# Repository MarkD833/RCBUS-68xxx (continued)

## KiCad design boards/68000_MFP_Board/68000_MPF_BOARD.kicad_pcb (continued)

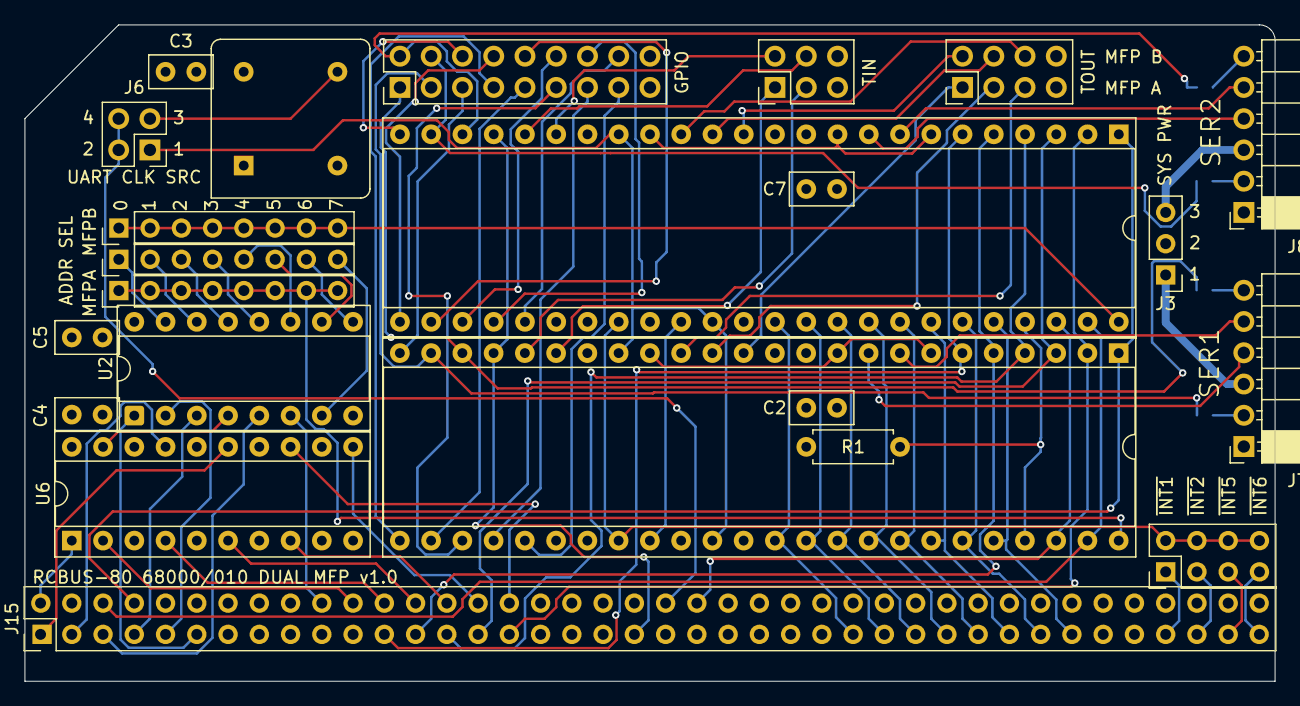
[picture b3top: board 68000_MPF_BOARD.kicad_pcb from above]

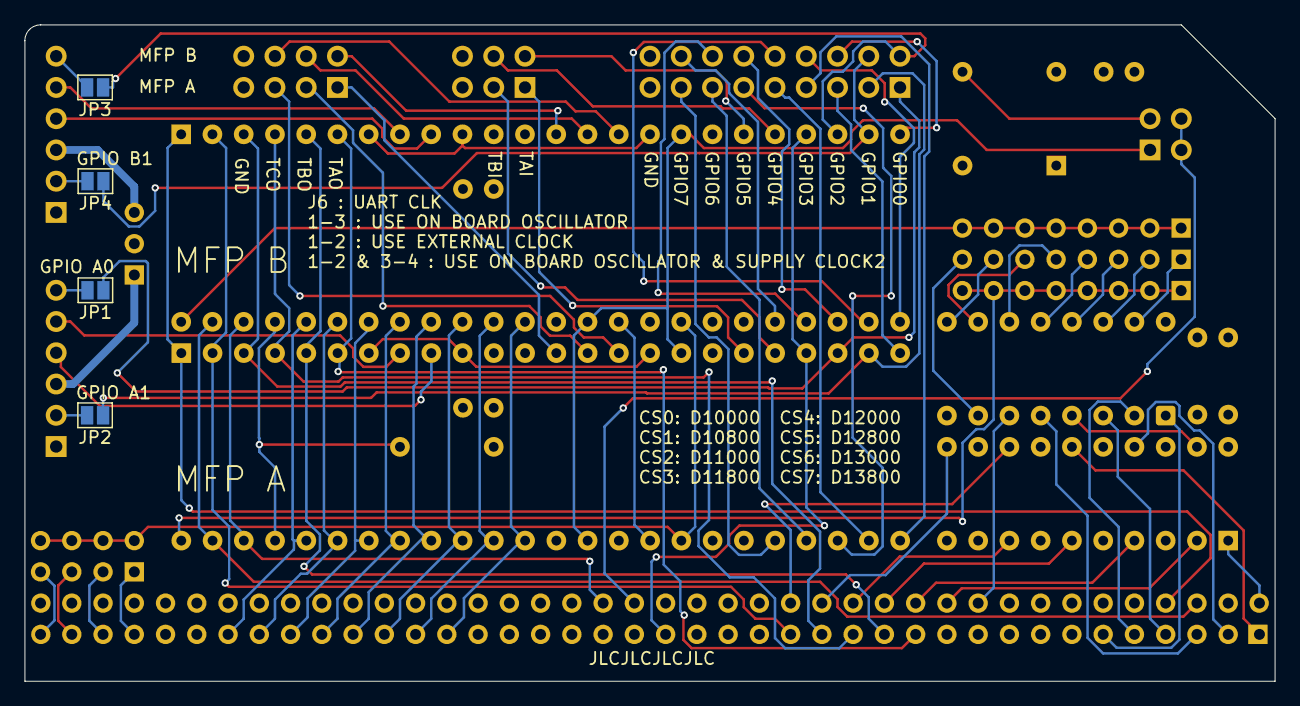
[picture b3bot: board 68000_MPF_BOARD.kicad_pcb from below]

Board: 4 copper layers, 101.6 x 53.3 mm, 27 parts (4 on the bottom side), 92 nets.

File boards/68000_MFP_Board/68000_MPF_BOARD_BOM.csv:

"Reference","Value","Datasheet","Footprint","Qty","Description"
"C2,C3,C4,C5,C7","100n","~","Capacitor_THT:C_Disc_D5.0mm_W2.5mm_P2.50mm","5","Unpolarized ceramic capacitor"
"J2,J5","Conn_02x04_Odd_Even","~","Connector_PinHeader_2.54mm:PinHeader_2x04_P2.54mm_Vertical,MyLibrary2023:PinHeader_2x04_P2.54mm_Vertical","2","Generic connector, double row, 02x04,Generic connector, double row, 02x04, right angle"
"J3","Conn_01x03","~","MyLibrary2023:PinHeader_1x03_P2.54mm_Vertical","1","Generic connector, single row, 01x03"
"J4","Conn_02x09_Odd_Even","~","Connector_PinHeader_2.54mm:PinHeader_2x09_P2.54mm_Vertical","1","Generic connector, double row, 02x09, right angle"
"J6","Conn_02x02_Odd_Even","~","Connector_PinHeader_2.54mm:PinHeader_2x02_P2.54mm_Vertical","1","Generic connector, double row, 02x02"
"J7,J8","Conn_01x06","~","Connector_PinSocket_2.54mm:PinSocket_1x06_P2.54mm_Horizontal","2","Generic connector, single row, 01x06, right angle"
"J9,J11,J12","Conn_01x08","~","MyLibrary2023:PinHeader_1x08_P2.54mm_Vertical","3","Generic connector, single row, 01x08"
"J14","Conn_02x03_Odd_Even","~","Connector_PinHeader_2.54mm:PinHeader_2x03_P2.54mm_Vertical","1","Generic connector, double row, 02x03, right angle"
"J15","RCBus_80PIN_68000","~","MyLibrary2023:RCBus_80p_Medium","1","Generic connector, double row, 02x20, right angle"
"JP1,JP2,JP3,JP4","SolderJumper","~","Jumper:SolderJumper-2_P1.3mm_Open_Pad1.0x1.5mm","4","Solder Jumper, 2-pole, open"
"R1","10K","~","Resistor_THT:R_Axial_DIN0207_L6.3mm_D2.5mm_P7.62mm_Horizontal","1",""
"U2","74LS138","http://www.ti.com/lit/gpn/sn74LS138","Package_DIP:DIP-16_W7.62mm_Socket","1","Decoder 3 to 8 active low outputs"
"U4,U5","68901P","","MyLibrary2023:DIP-48_W15.24mm_Socket","2","Multi-function peripheral device"
"U6","74LS688","http://www.ti.com/lit/gpn/sn74LS688","MyLibrary2023:DIP-20_W7.62mm_Socket","1","8-bit magnitude comparator"
"X1","CXO_DIP8","http://cdn-reichelt.de/documents/datenblatt/B400/OSZI.pdf","Oscillator:Oscillator_DIP-8","1","Crystal Clock Oscillator, DIP8-style metal package"

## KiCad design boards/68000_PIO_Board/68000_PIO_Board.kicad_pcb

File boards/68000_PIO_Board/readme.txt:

For some reason that I can't yet figure out, the 68230 board is very unreliable. The issue seems to be with the write timing as the chips always report the correct port pin levels during a read of the alternate data registers.

I've tried 68230s from ST and Mostek with a simple test program with the timer configured to output a square wave on PC3 whilst also toggling pin PA0 in software. I'm getting all combinations of results from no pin activity, only PA0 toggles, only PC3 toggles and both PA0 and PC3 toggling.

I know the code works as a PLCC 68230 (Freescale badged) on another 68000 system I have works correctly.

NOTE:
=====
* The 68230 needs a clock signal in order to function correctly, even if the
  timer is not being used. Set J2 and J6 for your choice of clock source.

ERRORS:
======= 
* The 68230 chip select has to include one of the /nDS signals not just /AS.
  Fix by cutting the /AS track between RCBus pin 41 and the 74LS688 pin 1.
  Add a wire link between RCBus pin 43 (/LDS) and the 74LS688 pin 1.

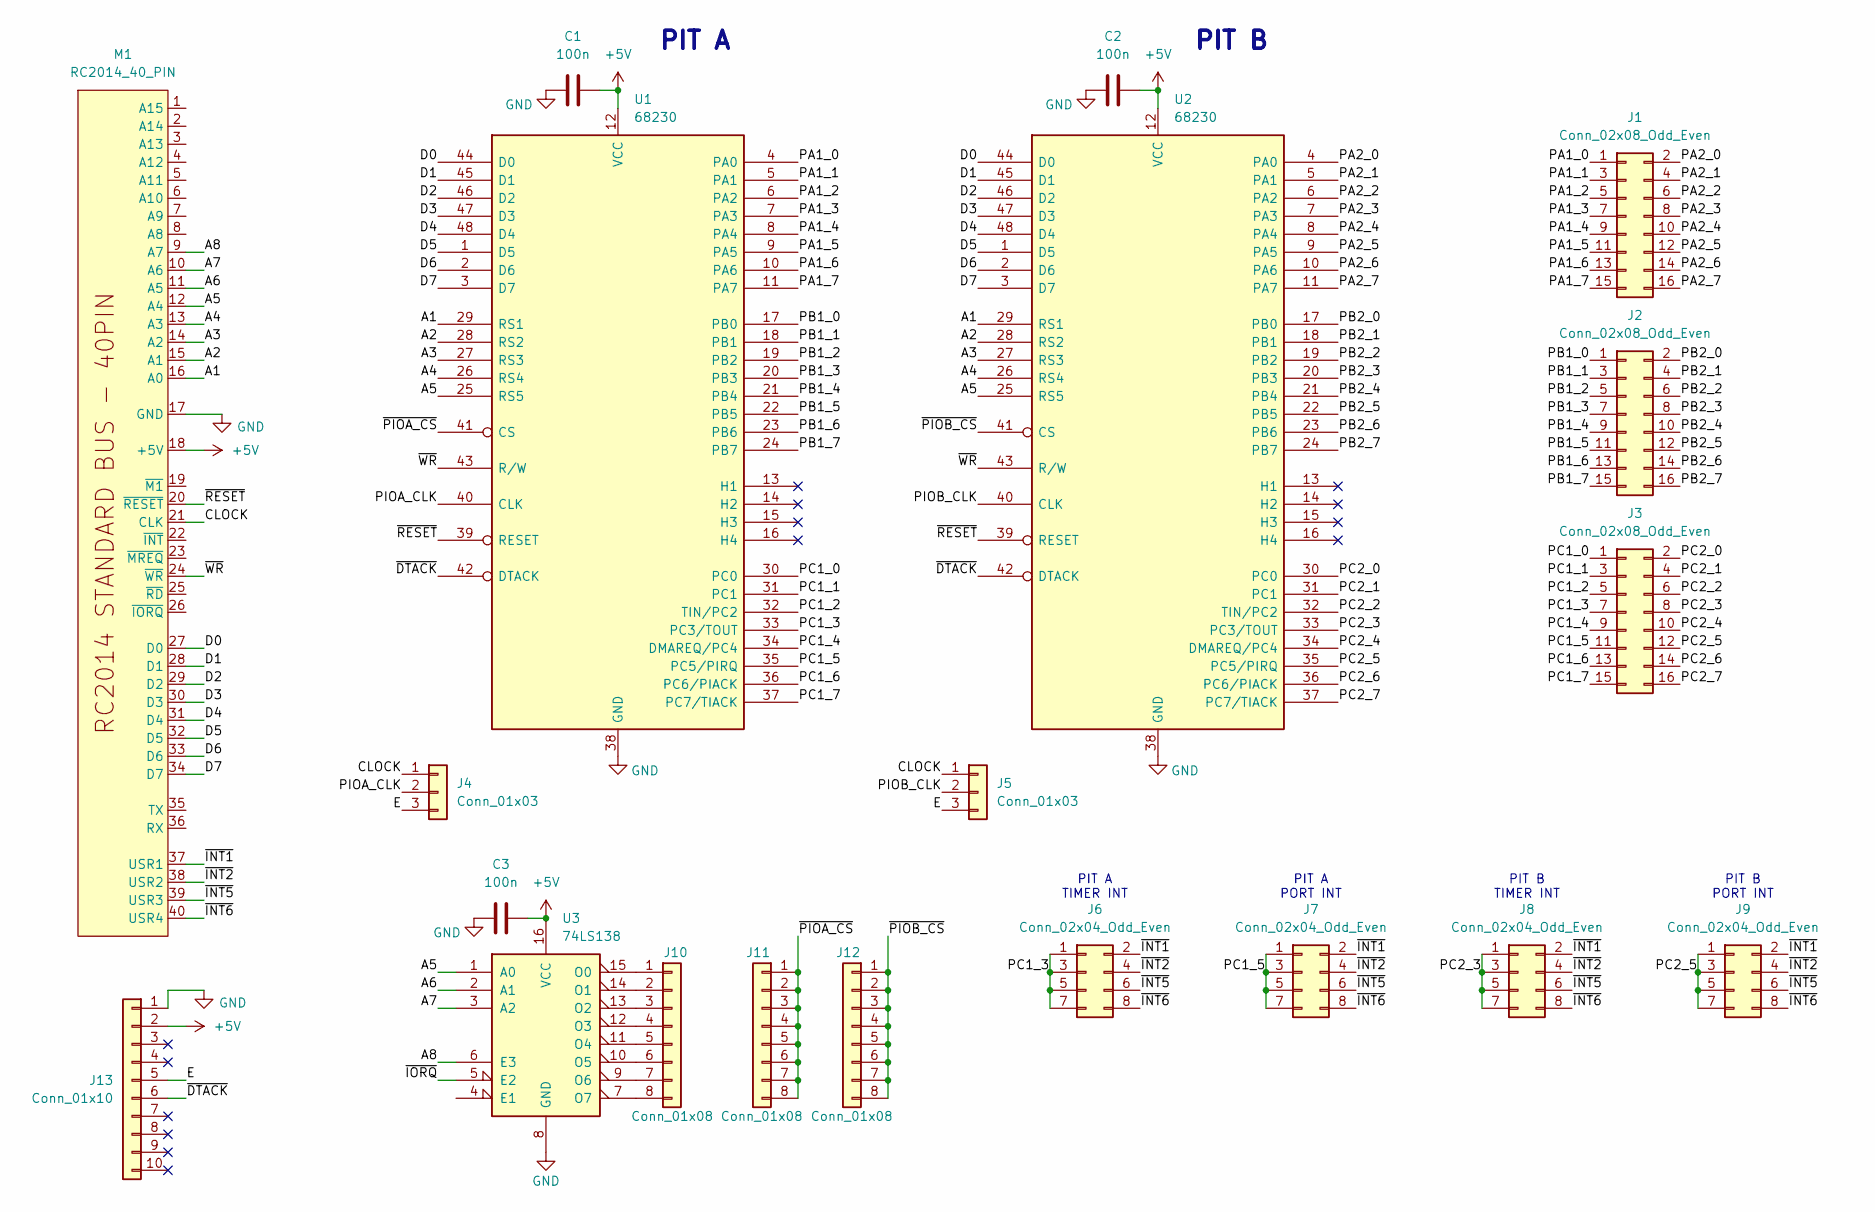
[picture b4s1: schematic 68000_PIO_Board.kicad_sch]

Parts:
C1, C2, C3: 100n; C_Disc_D5.0mm_W2.5mm_P2.50mm
J1, J2, J3: Conn_02x08_Odd_Even; PinHeader_2x08_P2.54mm_Vertical
J4, J5: Conn_01x03; PinHeader_1x03_P2.54mm_Vertical
J6, J7, J8, J9: Conn_02x04_Odd_Even; PinHeader_2x04_P2.54mm_Vertical
J10, J11, J12: Conn_01x08; PinHeader_1x08_P2.54mm_Vertical
J13: Conn_01x10; PinHeader_1x10_P2.54mm_Vertical
M1: RC2014_40_PIN; RC2014_STD_40_PIN
U1, U2: 68230; DIP-48_W15.24mm_Socket
U3: 74LS138; DIP-16_W7.62mm_Socket

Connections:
+5V: C1.1, C2.1, C3.2, J13.2, M1.18 (+5V), U1.12 (VCC), U2.12 (VCC), U3.16 (VCC)
/A1: M1.16 (A0), U1.29 (RS1), U2.29 (RS1)
/A2: M1.15 (A1), U1.28 (RS2), U2.28 (RS2)
/A3: M1.14 (A2), U1.27 (RS3), U2.27 (RS3)
/A4: M1.13 (A3), U1.26 (RS4), U2.26 (RS4)
/A5: M1.12 (A4), U1.25 (RS5), U2.25 (RS5), U3.1 (A0)
/A6: M1.11 (A5), U3.2 (A1)
/A7: M1.10 (A6), U3.3 (A2)
/A8: M1.9 (A7), U3.6 (E3)
/CLOCK: J4.1, J5.1, M1.21 (CLK)
/D0: M1.27 (D0), U1.44 (D0), U2.44 (D0)
/D1: M1.28 (D1), U1.45 (D1), U2.45 (D1)
/D2: M1.29 (D2), U1.46 (D2), U2.46 (D2)
/D3: M1.30 (D3), U1.47 (D3), U2.47 (D3)
/D4: M1.31 (D4), U1.48 (D4), U2.48 (D4)
/D5: M1.32 (D5), U1.1 (D5), U2.1 (D5)
/D6: M1.33 (D6), U1.2 (D6), U2.2 (D6)
/D7: M1.34 (D7), U1.3 (D7), U2.3 (D7)
/E: J4.3, J5.3, J13.5
/PA1_0: J1.1, U1.4 (PA0)
/PA1_1: J1.3, U1.5 (PA1)
/PA1_2: J1.5, U1.6 (PA2)
/PA1_3: J1.7, U1.7 (PA3)
/PA1_4: J1.9, U1.8 (PA4)
/PA1_5: J1.11, U1.9 (PA5)
/PA1_6: J1.13, U1.10 (PA6)
/PA1_7: J1.15, U1.11 (PA7)
/PA2_0: J1.2, U2.4 (PA0)
/PA2_1: J1.4, U2.5 (PA1)
/PA2_2: J1.6, U2.6 (PA2)
/PA2_3: J1.8, U2.7 (PA3)
/PA2_4: J1.10, U2.8 (PA4)
/PA2_5: J1.12, U2.9 (PA5)
/PA2_6: J1.14, U2.10 (PA6)
/PA2_7: J1.16, U2.11 (PA7)
/PB1_0: J2.1, U1.17 (PB0)
/PB1_1: J2.3, U1.18 (PB1)
/PB1_2: J2.5, U1.19 (PB2)
/PB1_3: J2.7, U1.20 (PB3)
/PB1_4: J2.9, U1.21 (PB4)
/PB1_5: J2.11, U1.22 (PB5)
/PB1_6: J2.13, U1.23 (PB6)
/PB1_7: J2.15, U1.24 (PB7)
/PB2_0: J2.2, U2.17 (PB0)
/PB2_1: J2.4, U2.18 (PB1)
/PB2_2: J2.6, U2.19 (PB2)
/PB2_3: J2.8, U2.20 (PB3)
/PB2_4: J2.10, U2.21 (PB4)
/PB2_5: J2.12, U2.22 (PB5)
/PB2_6: J2.14, U2.23 (PB6)
/PB2_7: J2.16, U2.24 (PB7)
/PC1_0: J3.1, U1.30 (PC0)
/PC1_1: J3.3, U1.31 (PC1)
/PC1_2: J3.5, U1.32 (TIN/PC2)
/PC1_3: J3.7, J6.1, J6.3, J6.5, J6.7, U1.33 (PC3/TOUT)
/PC1_4: J3.9, U1.34 (DMAREQ/PC4)
/PC1_5: J3.11, J7.1, J7.3, J7.5, J7.7, U1.35 (PC5/PIRQ)
/PC1_6: J3.13, U1.36 (PC6/PIACK)
/PC1_7: J3.15, U1.37 (PC7/TIACK)
/PC2_0: J3.2, U2.30 (PC0)
/PC2_1: J3.4, U2.31 (PC1)
/PC2_2: J3.6, U2.32 (TIN/PC2)
/PC2_3: J3.8, J8.1, J8.3, J8.5, J8.7, U2.33 (PC3/TOUT)
/PC2_4: J3.10, U2.34 (DMAREQ/PC4)
/PC2_5: J3.12, J9.1, J9.3, J9.5, J9.7, U2.35 (PC5/PIRQ)
/PC2_6: J3.14, U2.36 (PC6/PIACK)
/PC2_7: J3.16, U2.37 (PC7/TIACK)
/PIOA_CLK: J4.2, U1.40 (CLK)
/PIOB_CLK: J5.2, U2.40 (CLK)
/~DTACK: J13.6, U1.42 (DTACK), U2.42 (DTACK)
/~INT1: J6.2, J7.2, J8.2, J9.2, M1.37 (USR1)
/~INT2: J6.4, J7.4, J8.4, J9.4, M1.38 (USR2)
/~INT5: J6.6, J7.6, J8.6, J9.6, M1.39 (USR3)
/~INT6: J6.8, J7.8, J8.8, J9.8, M1.40 (USR4)
/~IORQ: U3.5 (E2)
/~PIOA_CS: J11.1, J11.2, J11.3, J11.4, J11.5, J11.6, J11.7, J11.8, U1.41 (CS)
/~PIOB_CS: J12.1, J12.2, J12.3, J12.4, J12.5, J12.6, J12.7, J12.8, U2.41 (CS)
/~RESET: M1.20 (~RESET), U1.39 (RESET), U2.39 (RESET)
/~WR: M1.24 (~WR), U1.43 (R/W), U2.43 (R/W)
GND: C1.2, C2.2, C3.1, J13.1, M1.17 (GND), U1.38 (GND), U2.38 (GND), U3.8 (GND)
unnamed: J10.1, U3.15 (O0)
unnamed: J10.2, U3.14 (O1)
unnamed: J10.3, U3.13 (O2)
unnamed: J10.4, U3.12 (O3)
unnamed: J10.5, U3.11 (O4)
unnamed: J10.6, U3.10 (O5)
unnamed: J10.7, U3.9 (O6)
unnamed: J10.8, U3.7 (O7)

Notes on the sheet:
PIT B PORT INT
PIT A PORT INT
PIT B
PIT A TIMER INT
PIT B TIMER INT
PIT A

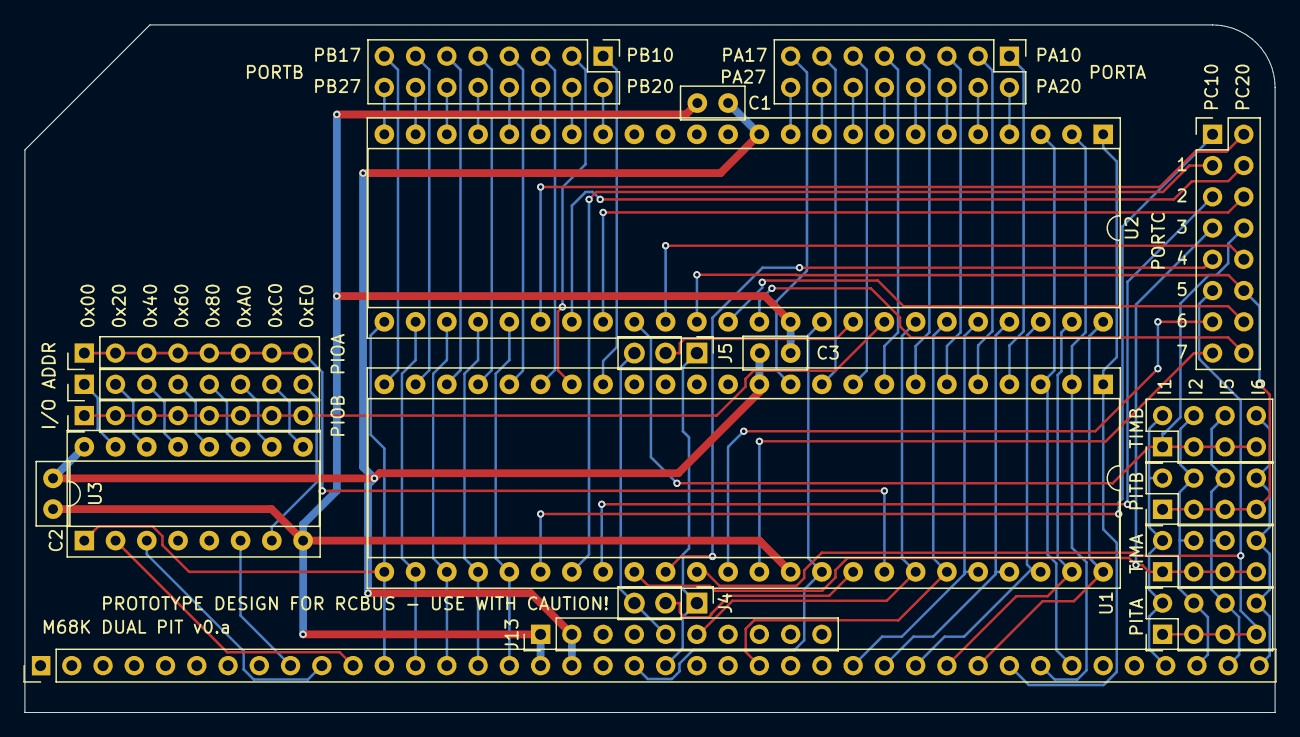
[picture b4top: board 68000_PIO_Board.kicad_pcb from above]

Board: 2 copper layers, 101.6 x 55.9 mm, 20 parts (0 on the bottom side), 87 nets.

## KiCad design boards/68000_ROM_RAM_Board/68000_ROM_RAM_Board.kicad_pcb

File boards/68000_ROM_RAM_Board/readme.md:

# ROM & RAM board - V1 - 128K ROM + 1M RAM

# Details
The ROM & RAM board is designed to plug into an RCBus-80 backplane with support for 128K ROM (via 2x Winbond W27C512 EEPROMs) and 1M RAM (via 2x Alliance Memory AS6C4008 SRAMs). The EEPROMs and SRAMs are used as a pair to allow 16-bit wide memory accesses.

## Address Decoding
The address decoding is carried out by a 74LS138 and divides the lower 8Mb of memory space into eight 1Mb blocks. The EEPROMs are hard wired to /CS0 (pin 15) and the SRAMs are hard wired to /CS1 (pin 14). This configuration always places the EEPROMs starting at address 0x000000 and the SRAMs starting at address 0x100000.

## Bus Width 
A 74LS139 generates the read and write signals for each of the memory chips and takes care of byte or word accesses.

## DTACK
A 74LS125 is used to generate a simple /DTACK signal driven directly from the EEPROM and SRAM chip select signals without any wait period.

# Board Assembly
Assembly of the board should be fairly straightforward as there are no surface mount devices to deal with.

When fitting the 80-pin right angle connector, initially only solder a couple of pins at opposite ends of the connector so that you can make any adjustments if the board is not vertical when fitted to the backplane.

# Winbond W27C512 EEPROMs
Be careful where you source these devices from. I bought mine from AliExpress and they were sold as new. In fact they were salvaged from boards and the IC legs were tinned with solder. This makes the pins slightly "sticky" when you insert the chips into IC sockets. My experience with these chips is that you may get 6-10 insertions/removals before the IC socket spring contacts start to break.

# Errors
None so far.

# To Do
+ Experiment to find the maximum width of board that JLCPCB will accept to keep the low price.
+ Modify the RCBus80 medium board footprint in Kicad so that pins 1,40,41 & 80 don't throw DRC warnings/errors.

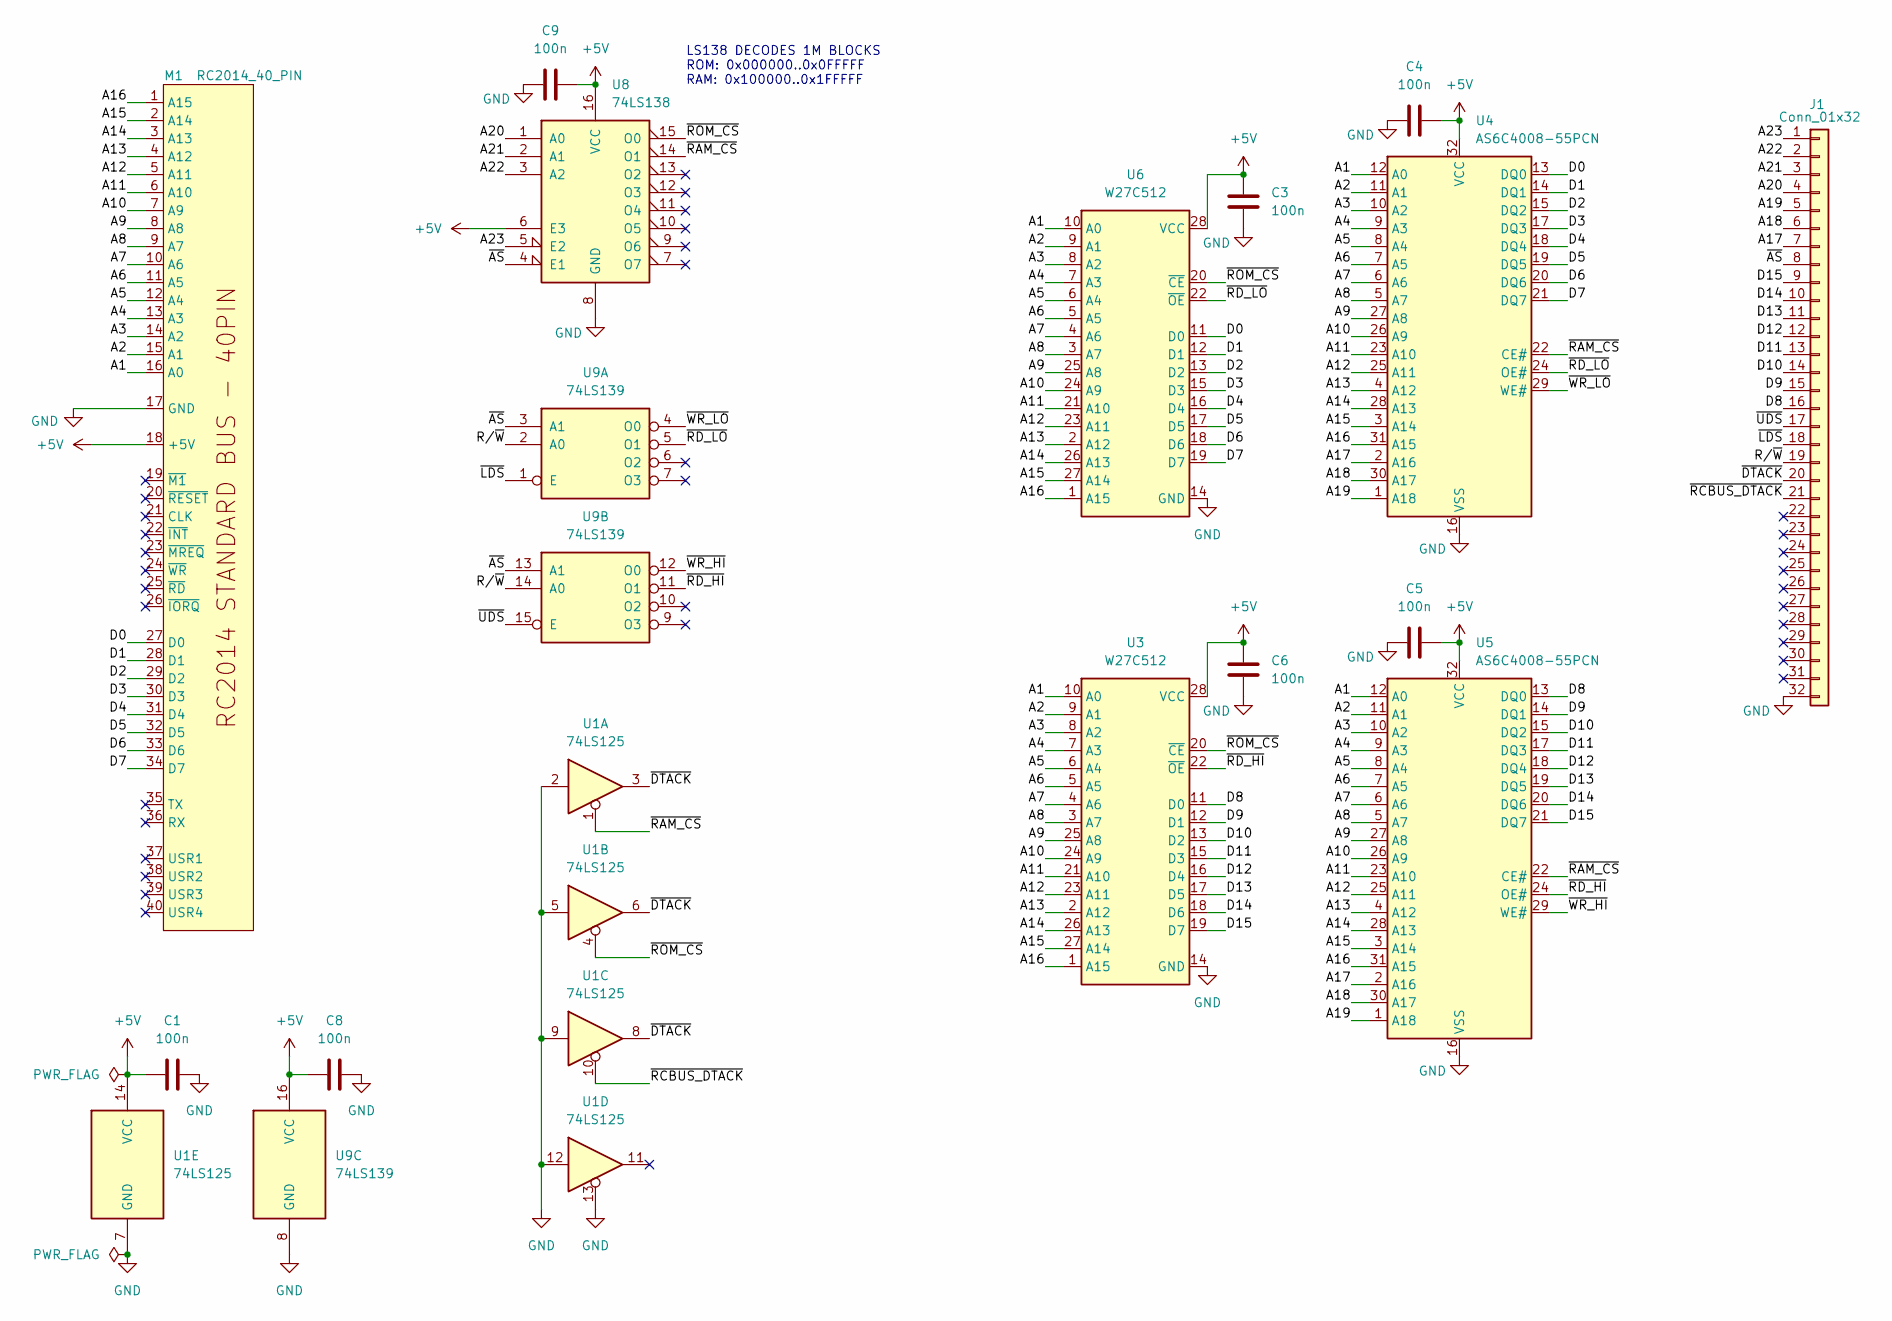
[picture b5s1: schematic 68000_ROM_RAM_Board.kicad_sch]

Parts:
C1, C3, C4, C5, C6, C8, C9: 100n; C_Disc_D5.0mm_W2.5mm_P2.50mm
J1: Conn_01x32; PinHeader_1x32_P2.54mm_Vertical
M1: RC2014_40_PIN; RC2014_STD_40_PIN
U1: 74LS125; DIP-14_W7.62mm_Socket
U3, U6: W27C512; DIP-28_W15.24mm
U4, U5: AS6C4008-55PCN; DIP-32_W15.24mm
U8: 74LS138; DIP-16_W7.62mm_Socket
U9: 74LS139; DIP-16_W7.62mm_Socket

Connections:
+5V: C1.1, C3.1, C4.2, C5.2, C6.1, C8.1, C9.2, M1.18 (+5V), U1.14 (VCC), U3.28 (VCC), U4.32 (VCC), U5.32 (VCC), U6.28 (VCC), U8.6 (E3), U8.16 (VCC), U9.16 (VCC)
/A1: M1.16 (A0), U3.10 (A0), U4.12 (A0), U5.12 (A0), U6.10 (A0)
/A2: M1.15 (A1), U3.9 (A1), U4.11 (A1), U5.11 (A1), U6.9 (A1)
/A3: M1.14 (A2), U3.8 (A2), U4.10 (A2), U5.10 (A2), U6.8 (A2)
/A4: M1.13 (A3), U3.7 (A3), U4.9 (A3), U5.9 (A3), U6.7 (A3)
/A5: M1.12 (A4), U3.6 (A4), U4.8 (A4), U5.8 (A4), U6.6 (A4)
/A6: M1.11 (A5), U3.5 (A5), U4.7 (A5), U5.7 (A5), U6.5 (A5)
/A7: M1.10 (A6), U3.4 (A6), U4.6 (A6), U5.6 (A6), U6.4 (A6)
/A8: M1.9 (A7), U3.3 (A7), U4.5 (A7), U5.5 (A7), U6.3 (A7)
/A9: M1.8 (A8), U3.25 (A8), U4.27 (A8), U5.27 (A8), U6.25 (A8)
/A10: M1.7 (A9), U3.24 (A9), U4.26 (A9), U5.26 (A9), U6.24 (A9)
/A11: M1.6 (A10), U3.21 (A10), U4.23 (A10), U5.23 (A10), U6.21 (A10)
/A12: M1.5 (A11), U3.23 (A11), U4.25 (A11), U5.25 (A11), U6.23 (A11)
/A13: M1.4 (A12), U3.2 (A12), U4.4 (A12), U5.4 (A12), U6.2 (A12)
/A14: M1.3 (A13), U3.26 (A13), U4.28 (A13), U5.28 (A13), U6.26 (A13)
/A15: M1.2 (A14), U3.27 (A14), U4.3 (A14), U5.3 (A14), U6.27 (A14)
/A16: M1.1 (A15), U3.1 (A15), U4.31 (A15), U5.31 (A15), U6.1 (A15)
/A17: J1.7, U4.2 (A16), U5.2 (A16)
/A18: J1.6, U4.30 (A17), U5.30 (A17)
/A19: J1.5, U4.1 (A18), U5.1 (A18)
/A20: J1.4, U8.1 (A0)
/A21: J1.3, U8.2 (A1)
/A22: J1.2, U8.3 (A2)
/A23: J1.1, U8.5 (E2)
/D0: M1.27 (D0), U4.13 (DQ0), U6.11 (D0)
/D1: M1.28 (D1), U4.14 (DQ1), U6.12 (D1)
/D2: M1.29 (D2), U4.15 (DQ2), U6.13 (D2)
/D3: M1.30 (D3), U4.17 (DQ3), U6.15 (D3)
/D4: M1.31 (D4), U4.18 (DQ4), U6.16 (D4)
/D5: M1.32 (D5), U4.19 (DQ5), U6.17 (D5)
/D6: M1.33 (D6), U4.20 (DQ6), U6.18 (D6)
/D7: M1.34 (D7), U4.21 (DQ7), U6.19 (D7)
/D8: J1.16, U3.11 (D0), U5.13 (DQ0)
/D9: J1.15, U3.12 (D1), U5.14 (DQ1)
/D10: J1.14, U3.13 (D2), U5.15 (DQ2)
/D11: J1.13, U3.15 (D3), U5.17 (DQ3)
/D12: J1.12, U3.16 (D4), U5.18 (DQ4)
/D13: J1.11, U3.17 (D5), U5.19 (DQ5)
/D14: J1.10, U3.18 (D6), U5.20 (DQ6)
/D15: J1.9, U3.19 (D7), U5.21 (DQ7)
/R/~W: J1.19, U9.2 (A0), U9.14 (A0)
/~AS: J1.8, U8.4 (E1), U9.3 (A1), U9.13 (A1)
/~DTACK: J1.20, U1.3, U1.6, U1.8
/~LDS: J1.18, U9.1 (E)
/~RAM_CS: U1.1, U4.22 (CE#), U5.22 (CE#), U8.14 (O1)
/~RCBUS_DTACK: J1.21, U1.10
/~RD_HI: U3.22 (~OE), U5.24 (OE#), U9.11 (O1)
/~RD_LO: U4.24 (OE#), U6.22 (~OE), U9.5 (O1)
/~ROM_CS: U1.4, U3.20 (~CE), U6.20 (~CE), U8.15 (O0)
/~UDS: J1.17, U9.15 (E)
/~WR_HI: U5.29 (WE#), U9.12 (O0)
/~WR_LO: U4.29 (WE#), U9.4 (O0)
GND: C1.2, C3.2, C4.1, C5.1, C6.2, C8.2, C9.1, J1.32, M1.17 (GND), U1.2, U1.5, U1.7 (GND), U1.9, U1.12, U1.13, U3.14 (GND), U4.16 (VSS), U5.16 (VSS), U6.14 (GND), U8.8 (GND), U9.8 (GND)

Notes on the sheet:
LS138 DECODES 1M BLOCKS ROM: 0x000000..0x0FFFFF RAM: 0x100000..0x1FFFFF

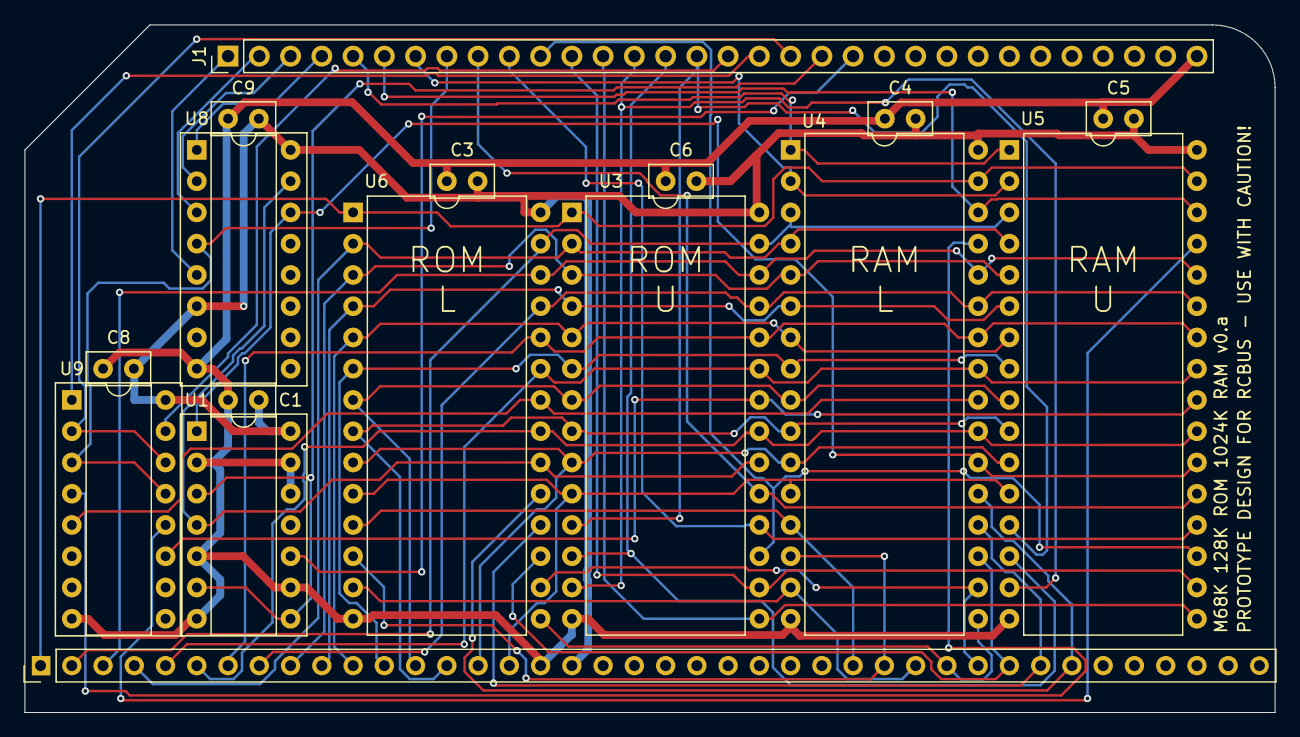
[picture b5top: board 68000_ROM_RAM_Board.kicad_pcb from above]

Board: 2 copper layers, 101.6 x 55.9 mm, 16 parts (0 on the bottom side), 53 nets.

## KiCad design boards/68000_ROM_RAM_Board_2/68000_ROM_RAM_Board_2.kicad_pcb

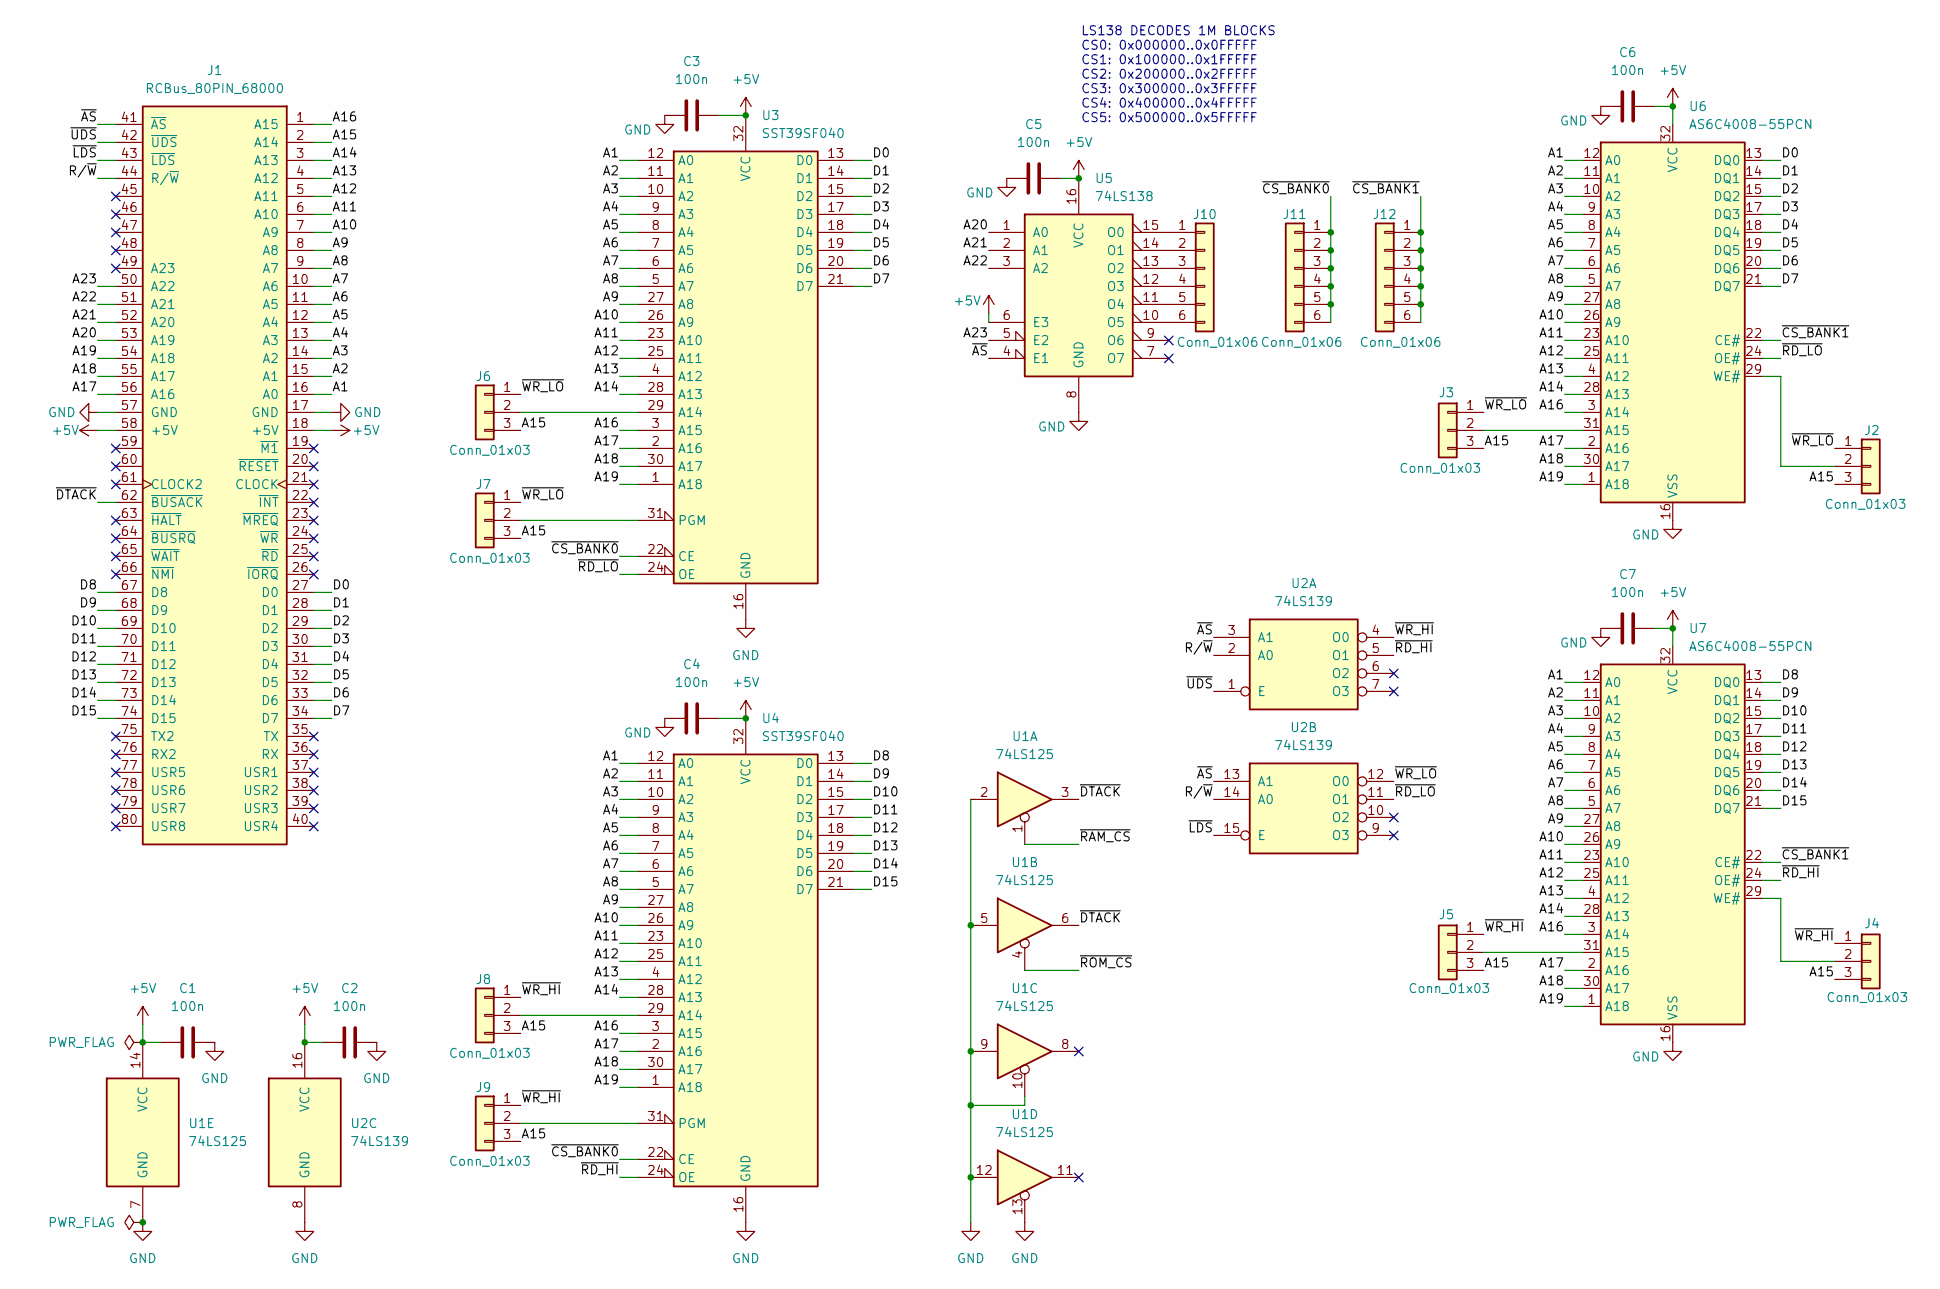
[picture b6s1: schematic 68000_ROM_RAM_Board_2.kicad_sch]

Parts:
C1, C2, C3, C4, C5, C6, C7: 100n; C_Disc_D5.0mm_W2.5mm_P2.50mm
J1: RCBus_80PIN_68000; RCBus_80p_Medium
J2, J3, J4, J5, J6, J7, J8, J9: Conn_01x03; PinHeader_1x03_P2.54mm_Vertical
J10, J11, J12: Conn_01x06; PinHeader_1x06_P2.54mm_Vertical
U1: 74LS125; DIP-14_W7.62mm
U2: 74LS139; DIP-16_W7.62mm
U3, U4: SST39SF040; DIP-32_W15.24mm
U5: 74LS138; DIP-16_W7.62mm
U6, U7: AS6C4008-55PCN; DIP-32_W15.24mm

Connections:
+5V: C1.1, C2.1, C3.2, C4.2, C5.2, C6.2, C7.2, J1.18 (+5V), J1.58 (+5V), U1.14 (VCC), U2.16 (VCC), U3.32 (VCC), U4.32 (VCC), U5.6 (E3), U5.16 (VCC), U6.32 (VCC), U7.32 (VCC)
/A1: J1.16 (A0), U3.12 (A0), U4.12 (A0), U6.12 (A0), U7.12 (A0)
/A2: J1.15 (A1), U3.11 (A1), U4.11 (A1), U6.11 (A1), U7.11 (A1)
/A3: J1.14 (A2), U3.10 (A2), U4.10 (A2), U6.10 (A2), U7.10 (A2)
/A4: J1.13 (A3), U3.9 (A3), U4.9 (A3), U6.9 (A3), U7.9 (A3)
/A5: J1.12 (A4), U3.8 (A4), U4.8 (A4), U6.8 (A4), U7.8 (A4)
/A6: J1.11 (A5), U3.7 (A5), U4.7 (A5), U6.7 (A5), U7.7 (A5)
/A7: J1.10 (A6), U3.6 (A6), U4.6 (A6), U6.6 (A6), U7.6 (A6)
/A8: J1.9 (A7), U3.5 (A7), U4.5 (A7), U6.5 (A7), U7.5 (A7)
/A9: J1.8 (A8), U3.27 (A8), U4.27 (A8), U6.27 (A8), U7.27 (A8)
/A10: J1.7 (A9), U3.26 (A9), U4.26 (A9), U6.26 (A9), U7.26 (A9)
/A11: J1.6 (A10), U3.23 (A10), U4.23 (A10), U6.23 (A10), U7.23 (A10)
/A12: J1.5 (A11), U3.25 (A11), U4.25 (A11), U6.25 (A11), U7.25 (A11)
/A13: J1.4 (A12), U3.4 (A12), U4.4 (A12), U6.4 (A12), U7.4 (A12)
/A14: J1.3 (A13), U3.28 (A13), U4.28 (A13), U6.28 (A13), U7.28 (A13)
/A15: J1.2 (A14), J2.3, J3.3, J4.3, J5.3, J6.3, J7.3, J8.3, J9.3
/A16: J1.1 (A15), U3.3 (A15), U4.3 (A15), U6.3 (A14), U7.3 (A14)
/A17: J1.56 (A16), U3.2 (A16), U4.2 (A16), U6.2 (A16), U7.2 (A16)
/A18: J1.55 (A17), U3.30 (A17), U4.30 (A17), U6.30 (A17), U7.30 (A17)
/A19: J1.54 (A18), U3.1 (A18), U4.1 (A18), U6.1 (A18), U7.1 (A18)
/A20: J1.53 (A19), U5.1 (A0)
/A21: J1.52 (A20), U5.2 (A1)
/A22: J1.51 (A21), U5.3 (A2)
/A23: J1.50 (A22), U5.5 (E2)
/D0: J1.27 (D0), U3.13 (D0), U6.13 (DQ0)
/D1: J1.28 (D1), U3.14 (D1), U6.14 (DQ1)
/D2: J1.29 (D2), U3.15 (D2), U6.15 (DQ2)
/D3: J1.30 (D3), U3.17 (D3), U6.17 (DQ3)
/D4: J1.31 (D4), U3.18 (D4), U6.18 (DQ4)
/D5: J1.32 (D5), U3.19 (D5), U6.19 (DQ5)
/D6: J1.33 (D6), U3.20 (D6), U6.20 (DQ6)
/D7: J1.34 (D7), U3.21 (D7), U6.21 (DQ7)
/D8: J1.67 (D8), U4.13 (D0), U7.13 (DQ0)
/D9: J1.68 (D9), U4.14 (D1), U7.14 (DQ1)
/D10: J1.69 (D10), U4.15 (D2), U7.15 (DQ2)
/D11: J1.70 (D11), U4.17 (D3), U7.17 (DQ3)
/D12: J1.71 (D12), U4.18 (D4), U7.18 (DQ4)
/D13: J1.72 (D13), U4.19 (D5), U7.19 (DQ5)
/D14: J1.73 (D14), U4.20 (D6), U7.20 (DQ6)
/D15: J1.74 (D15), U4.21 (D7), U7.21 (DQ7)
/R/~W: J1.44 (R/~W), U2.2 (A0), U2.14 (A0)
/~AS: J1.41 (~AS), U2.3 (A1), U2.13 (A1), U5.4 (E1)
/~CS_BANK0: J11.1, J11.2, J11.3, J11.4, J11.5, J11.6, U3.22 (CE), U4.22 (CE)
/~CS_BANK1: J12.1, J12.2, J12.3, J12.4, J12.5, J12.6, U6.22 (CE#), U7.22 (CE#)
/~DTACK: J1.62 (~BUSACK), U1.3, U1.6
/~LDS: J1.43 (~LDS), U2.15 (E)
/~RAM_CS: U1.1
/~RD_HI: U2.5 (O1), U4.24 (OE), U7.24 (OE#)
/~RD_LO: U2.11 (O1), U3.24 (OE), U6.24 (OE#)
/~ROM_CS: U1.4
/~UDS: J1.42 (~UDS), U2.1 (E)
/~WR_HI: J4.1, J5.1, J8.1, J9.1, U2.4 (O0)
/~WR_LO: J2.1, J3.1, J6.1, J7.1, U2.12 (O0)
GND: C1.2, C2.2, C3.1, C4.1, C5.1, C6.1, C7.1, J1.17 (GND), J1.57 (GND), U1.2, U1.5, U1.7 (GND), U1.9, U1.10, U1.12, U1.13, U2.8 (GND), U3.16 (GND), U4.16 (GND), U5.8 (GND), U6.16 (VSS), U7.16 (VSS)
unnamed: J2.2, U6.29 (WE#)
unnamed: J3.2, U6.31 (A15)
unnamed: J4.2, U7.29 (WE#)
unnamed: J5.2, U7.31 (A15)
unnamed: J6.2, U3.29 (A14)
unnamed: J7.2, U3.31 (PGM)
unnamed: J8.2, U4.29 (A14)
unnamed: J9.2, U4.31 (PGM)
unnamed: J10.1, U5.15 (O0)
unnamed: J10.2, U5.14 (O1)
unnamed: J10.3, U5.13 (O2)
unnamed: J10.4, U5.12 (O3)
unnamed: J10.5, U5.11 (O4)
unnamed: J10.6, U5.10 (O5)

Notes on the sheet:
LS138 DECODES 1M BLOCKS CS0: 0x000000..0x0FFFFF CS1: 0x100000..0x1FFFFF CS2: 0x200000..0x2FFFFF CS3: 0x300000..0x3FFFFF CS4: 0x400000..0x4FFFFF CS5: 0x500000..0x5FFFFF

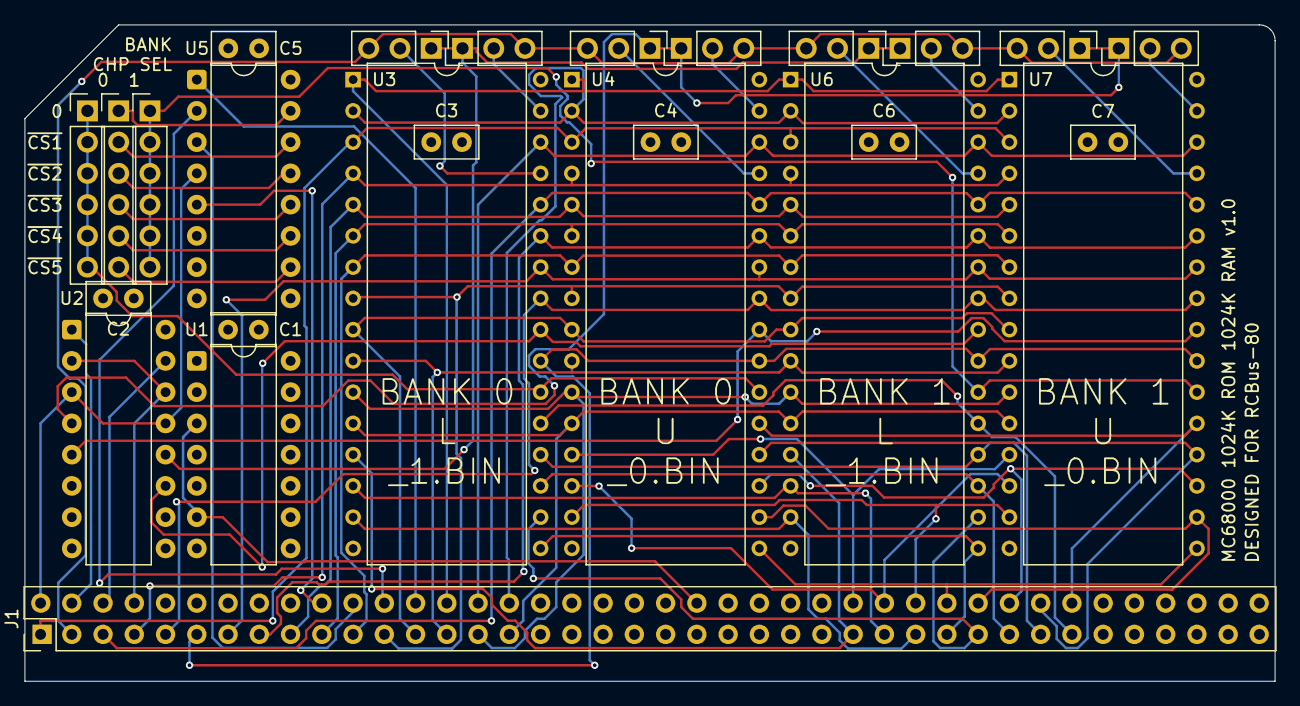
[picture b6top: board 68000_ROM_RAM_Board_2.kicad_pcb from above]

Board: 4 copper layers, 101.6 x 53.3 mm, 26 parts (0 on the bottom side), 66 nets.

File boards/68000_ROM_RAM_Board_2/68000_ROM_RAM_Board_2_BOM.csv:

"Reference","Value","Datasheet","Footprint","Qty","Description"
"C1,C2,C3,C4,C5,C6,C7","100n","~","Capacitor_THT:C_Disc_D5.0mm_W2.5mm_P2.50mm","7","Unpolarized ceramic capacitor"
"J1","RCBus_80PIN_68000","~","MyLibrary2023:RCBus_80p_Medium","1","Generic connector, double row, 02x40, right angle"
"J2,J3,J4,J5,J6,J7,J8,J9","Conn_01x03","~","Connector_PinHeader_2.54mm:PinHeader_1x03_P2.54mm_Vertical","8","Generic connector, single row, 01x03"
"J10,J11,J12","Conn_01x06","~","Connector_PinHeader_2.54mm:PinHeader_1x06_P2.54mm_Vertical","3","Generic connector, single row, 01x06"
"U1","74LS125","http://www.ti.com/lit/gpn/sn74LS125","Package_DIP:DIP-14_W7.62mm","1","Quad buffer 3-State outputs"
"U2","74LS139","http://www.ti.com/lit/ds/symlink/sn74ls139a.pdf","Package_DIP:DIP-16_W7.62mm","1","Dual Decoder 1 of 4, Active low outputs"
"U3,U4","SST39SF040","http://ww1.microchip.com/downloads/en/DeviceDoc/25022B.pdf","MyLibrary2023:DIP-32_W15.24mm","2","Silicon Storage Technology (SSF) 512k x 8 Flash ROM"
"U5","74LS138","http://www.ti.com/lit/gpn/sn74LS138","Package_DIP:DIP-16_W7.62mm","1","Decoder 3 to 8 active low outputs"
"U6,U7","AS6C4008-55PCN","https://www.alliancememory.com/wp-content/uploads/pdf/AS6C4008.pdf","MyLibrary2023:DIP-32_W15.24mm","2","512K x 8 Low Power CMOS RAM, DIP-32"
